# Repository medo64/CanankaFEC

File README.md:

[CAN Bus Framework Expansion Card](https://medo64.com/cananka/)
===============================================================

Cananka allows for the computer control of a CAN bus. The control of device is
possible via serial port (SLCAN compatible, Windows/Linux) or via SocketCAN
network driver (Linux).

## CAN Bus Pinout

To connect to this board, one has to use a 4-pin JST XH connector. The following
table represents the pinout, pin 1 being on the left as looking into the
expansion card.

| # | Ref   | Description                     |
|--:|:-----:|---------------------------------|
| 1 | GND   | Ground connection               |
| 2 | CAN L | CAN low-side                    |
| 3 | CAN H | CAN high-side                   |
| 4 | V+    | Not connected                   |

As power consumption is low, wires can be almost any AWG. I would recommend
using 24 AWG wire 0.25 mm² as they allow for greater compatibility with other
connectors.

## LEDs

Left LED will blink on UART communication with computer (both sending toward and
receiving data from computer).

Right LED will blink on CAN bus activity.

## Other repositories

The following hardware version are also available:
* [Full](https://github.com/medo64/Cananka) (isolated and in the case)
* [Framework Expansion Card](https://github.com/medo64/CanankaFEC) (non-isolated, in framework expansion card format)
* [HAT](https://github.com/medo64/CanankaHAT) (intended for Raspberry Pi)

The following additional repositories might be of interest:
* [Firmware](https://github.com/medo64/Cananka.Firmware)
* [Protocol](https://github.com/medo64/Cananka.Firmware/blob/main/PROTOCOL.md)
* [Test software](https://github.com/medo64/Cananka.Software)

---
*You can check my blog and other projects at [www.medo64.com](https://www.medo64.com/electronics/).*

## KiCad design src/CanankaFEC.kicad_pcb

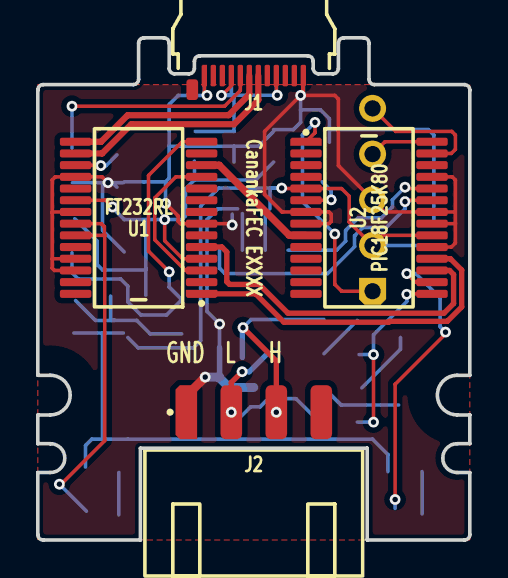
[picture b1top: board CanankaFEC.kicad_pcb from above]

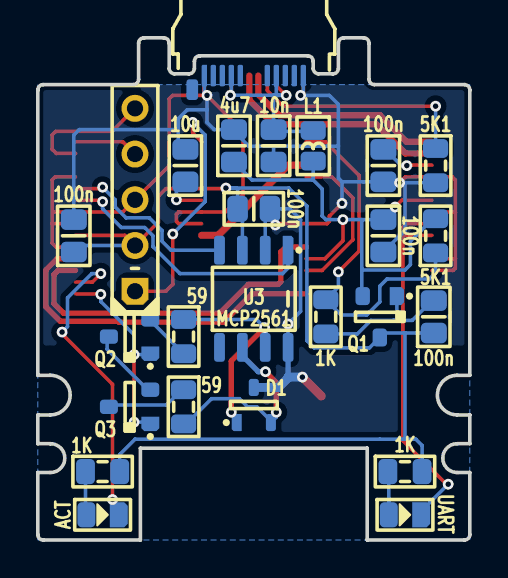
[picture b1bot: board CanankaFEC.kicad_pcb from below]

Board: 2 copper layers, 24.0 x 27.9 mm, 28 parts (24 on the bottom side), 30 nets.

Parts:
C1: 10n; C (0805)
C2, C3, C4, C5, C6: 100n; C (0805)
C7: 4u7; C (0805)
C8: 10u; C (0805)
D1: TVS; D TVS 24V [PESD24VL2BT,215] (SOT23-3)
DS1: UART; DS (0805)
DS2: ACT; DS (0805)
ICSP: Microchip PIC; ICSP PIC Pogo SS (5w)
J1: 105444-0001; J USB C 3.2 Edge (24w)
J2: B3B-XH-A; J JST XH Edge [CAN] (4w)
L1: 600R; L (0805)
Q1, Q2, Q3: BSS84; Q MOSFET-P (SOT23-3)
R1, R2: 59; R (0805)
R3, R4, R5: 1K; R (0805)
R6, R7: 5K1; R (0805)
U1: FT232RL; U Transceiver UART [FT232R] (SSOP-28)
U2: PIC18F25K80; U Micro [PIC18F25K80] (SSOP-28)
U3: MCP2561; U Transceiver CAN [MCP2561] (SOIC-8)

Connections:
3V3: C3.2, U1.17
5V: C2.2, C7.2, L1.1, Q1.2, R7.1, U1.4, U1.20
5V_SW: C4.2, C5.2, C6.2, ICSP.2, Q1.3, R3.1, R4.1, U2.5, U2.20, U3.3
A_CC: J1.A5, R6.2
CANRX: U2.24, U3.4
CANTX: U2.23, U3.1
CAN_H: D1.1, J2.3, R1.2, U3.7
CAN_H_TERM: Q2.2, R1.1
CAN_I_TERM: Q2.3, Q3.2
CAN_L: D1.2, J2.2, R2.1, U3.6
CAN_L_TERM: Q3.3, R2.2
CLOCK: U1.12, U2.9
GND: C1.1, C2.1, C3.1, C5.1, C6.1, C7.1, C8.1, D1.3, ICSP.3, J1.A1, J1.A12, J1.B01, J1.B12, J2.1, R6.1, U1.7, U1.18, U1.21, U1.25, U1.26, U2.7, U2.8, U2.19, U2.21, U2.22, U2.25, U3.2, U3.8
ICSP_CLK: ICSP.5, U2.27
ICSP_DAT: ICSP.4, U2.28
ICSP_VPP: ICSP.1, U2.1
IO_CONTROL_TERMINATE#: Q2.1, Q3.1, U2.15
LED_ACTIVITY: DS2.1, U2.16
LED_ACTIVITY': DS2.2, R4.2
LED_UART: DS1.1, U1.22, U1.23
LED_UART': DS1.2, R3.2
PWREN#: R5.1, R7.2, U1.14
PWREN#': C4.1, Q1.1, R5.2
RTS_CTS: U1.3, U1.11
RXD: U1.5, U2.17
TXD: U1.1, U2.18
USB_DM: J1.A7, U1.16
USB_DP: J1.A6, U1.15
USB_Vin: C1.2, J1.A4, J1.A9, J1.B04, J1.B09, L1.2
VDD_CORE: C8.2, U2.6

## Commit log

2023-11-13 Moved LEDs to bottom side
2023-12-26 Added PWREN pullup and moved LED 5V to switched
2023-12-30 Refactoring copper pour
2024-01-28 Moved silkscreen
2024-01-31 Moved TVS to bottom
2024-02-04 Swapped UART lines
2024-04-02 Updated connector designators
2024-06-05 Updated to KiCAD 8
2024-06-05 Moved termination resistor to bottom
2024-08-28 Updated diode footprint
2024-08-28 Added board designator
2024-08-28 Updated refdes
2024-08-28 Added transistor models
2024-09-08 Fixed termination mosfet setup
2024-09-08 Consolidating resistors a bit
2024-11-09 Added pin silkscreen
2024-11-10 Moved D1 refdes
2024-11-10 Fixed refdes
